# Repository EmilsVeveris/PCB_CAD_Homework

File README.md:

# PCB_CAD_Homework
Homework repository
Repositorija priekš majas darbiem kursa PCB CAD

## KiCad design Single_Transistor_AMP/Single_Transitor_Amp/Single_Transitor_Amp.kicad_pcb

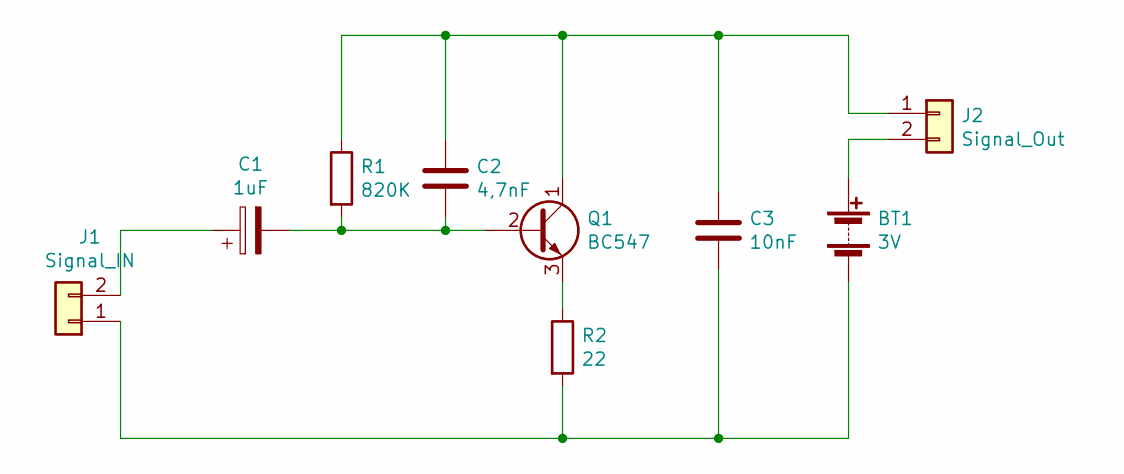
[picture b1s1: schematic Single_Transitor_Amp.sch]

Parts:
BT1: 3V; PinHeader_1x02_P1.27mm_Vertical
C1: 1uF; CP_Radial_D6.3mm_P2.50mm
C2: 4,7nF; C_0603_1608Metric
C3: 10nF; C_1206_3216Metric
J1: Signal_IN; PinHeader_1x02_P1.27mm_Vertical
J2: Signal_Out; PinHeader_1x02_P1.27mm_Vertical
Q1: BC547; TO-92
R1: 820K; R_0603_1608Metric
R2: 22; R_0603_1608Metric

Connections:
unnamed: BT1.1 (+), J2.2
unnamed: BT1.2 (-), C3.2, J1.1, R2.2
unnamed: C1.1, J1.2
unnamed: C1.2, C2.2, Q1.2 (B), R1.2
unnamed: C2.1, C3.1, J2.1, Q1.1 (C), R1.1
unnamed: Q1.3 (E), R2.1

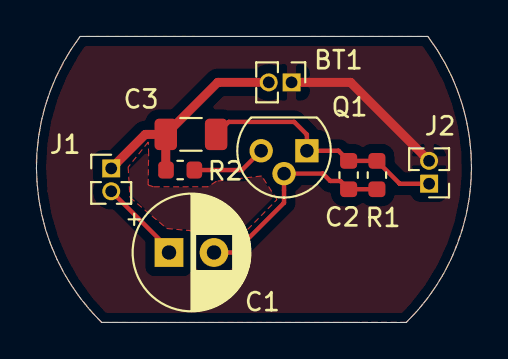
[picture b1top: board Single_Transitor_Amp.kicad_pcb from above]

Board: 4 copper layers, 24.2 x 15.9 mm, 9 parts (0 on the bottom side), 6 nets.

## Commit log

2020-02-25 Pirmais ieraksts
2020-02-26 Izveidota MultiVib principiālā shēma, 3 lekcijas Uzdevums
2020-02-26 Principiālā shēma MultiVibratoram
2020-03-04 3 lekcijas uzdevums
2020-03-11 Lekcija padaritais
2020-03-17 Pabeigts majasdarbs
2020-03-18 Trešais majas darbs, Viena tranzistora pastiprinatjas
2020-03-25 Treniņuzdevums
2020-03-25 Mājas darbs
2020-04-01 Majas Darbs par PCB darbavietas iestatīšnu
2020-04-15 15.04 Lekcijas Mājas darbs
2020-04-28 22.04 Lekcijas M.D
2020-05-05 Gerbera faili
2020-05-12 BOM un SVG faili
